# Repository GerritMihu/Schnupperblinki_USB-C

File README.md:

# Schnupperblinki_USB-C
 Schnupperübung für die Schupperschüler

 ## Bilder

## Exporte

- 3D-Ansichten:
  - [3D Top](./pic/3d_top.png)
  - [3D Bottom](./pic/3d_bottom.png)
  - [3D Isometrisch](./pic/3d_isometric.png)

- DXF (Layer-Exports): [dxf/](./dxf/)

### xTool Laser F2 Ultra — empfohlenes Vorgehensweise

- Empfohlen: zwei DXF-Dateien im dxf/-Ordner erzeugen:
  - Edge.Cuts → Schneidekante (äußerste Linie) — zum Schneiden
  - F.Cu     → Gravur (restliche Vektoren, kombiniert) 

Beispielbefehle:

# F.Cu (Gravur)
KICAD_CLI="kicad-cli" ./export_fcu_dxf.sh "Blinki mit USB-C.kicad_pcb" dxf

# Edge.Cuts (Schneiden)
flatpak run --command=kicad-cli org.kicad.KiCad pcb export dxf --layers Edge.Cuts --output-units mm --mode-single -o dxf "Blinki mit USB-C.kicad_pcb"

Hinweis: Die äußerste Linie (Edge.Cuts) ist die Schneidekante; der Rest wird als kombinierter Vektor für die Gravur genutzt. Falls Pfade gemerged oder Text in Konturen umgewandelt werden müssen, kann ein Zusatzskript oder Inkscape dafür genutzt; bei Bedarf hinzufügen.

## Bestückplan
[BOM (HTML-Preview)](https://htmlpreview.github.io/?https://github.com/GerritMihu/Schnupperblinki_USB-C/blob/main/bom/Blinki%20mit%20USB-C-ibom.html)

## Documentation exports

- PCB PDF: [Dok/Dok_PCB.pdf](./Dok/Dok_PCB.pdf)
- Schematic PDF: [Dok/Dok_SCH.pdf](./Dok/Dok_SCH.pdf)
- Schematic SVG: [Dok/Dok_SCH.svg](./Dok/Dok_SCH.svg)

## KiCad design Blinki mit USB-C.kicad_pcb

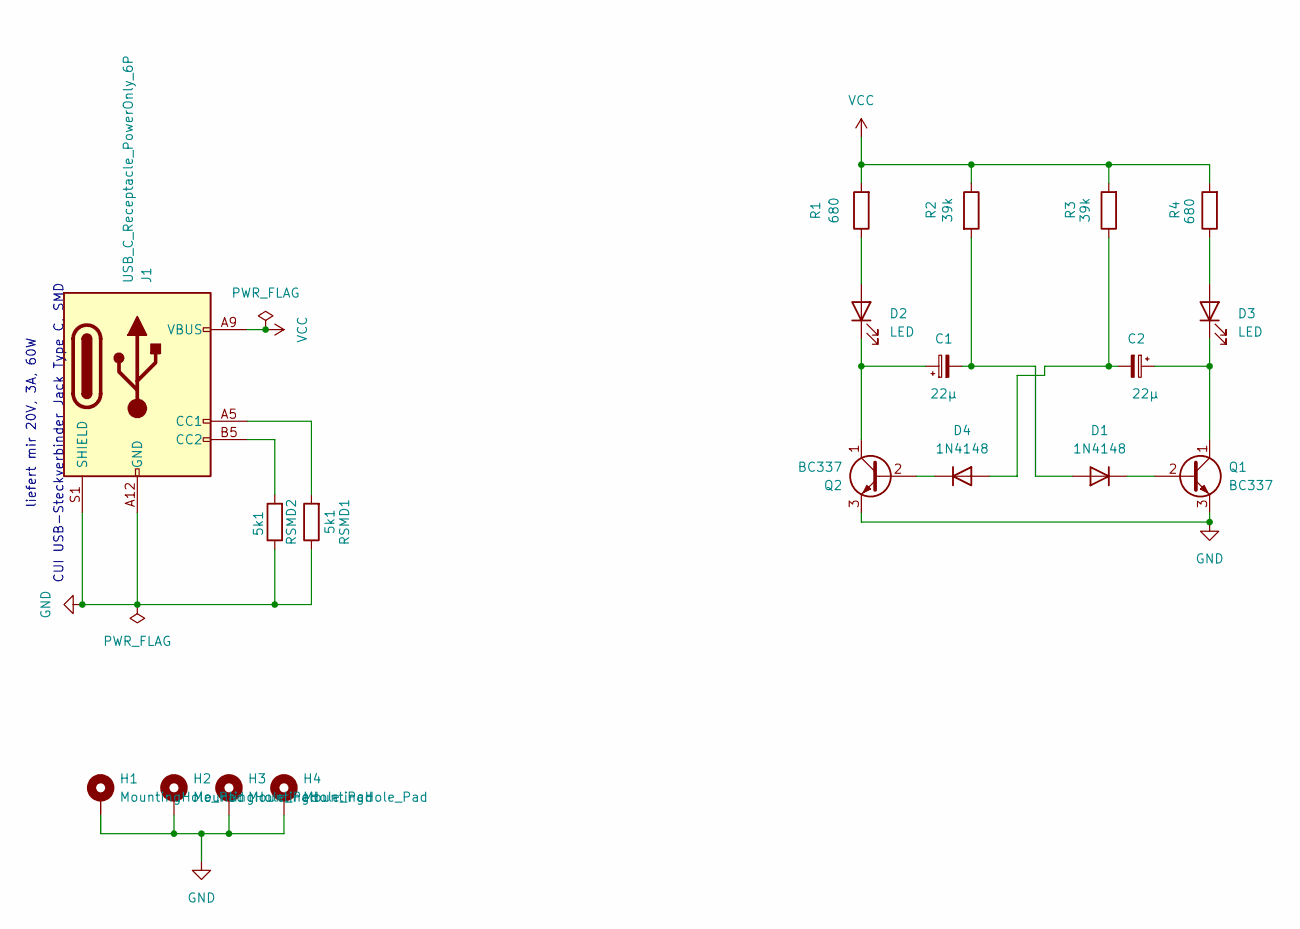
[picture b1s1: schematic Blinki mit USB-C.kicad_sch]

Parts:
C1, C2: 22µ; CP_Radial_D5.0mm_P2.50mm
D1, D4: 1N4148; D_DO-35_SOD27_P7.62mm_Horizontal
D2, D3: LED; LED_D3.0mm_FlatTop
H1, H2, H3, H4: MountingHole_Pad; MountingHole_3.2mm_M3
J1: USB_C_Receptacle_PowerOnly_6P
Q1, Q2: BC337; TO-92_Inline_Wide
R1, R4: 680; R_Axial_DIN0207_L6.3mm_D2.5mm_P10.16mm_Horizontal
R2, R3: 39k; R_Axial_DIN0207_L6.3mm_D2.5mm_P10.16mm_Horizontal
RSMD1, RSMD2: 5k1; R_0805_2012Metric_Pad1.20x1.40mm_HandSolder

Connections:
GND: H1.1, H2.1, H3.1, H4.1, J1.A12 (GND), J1.B12 (GND), J1.S1 (SHIELD), Q1.3 (E), Q2.3 (E), RSMD1.1, RSMD2.1
unnamed: C1.2, D1.2 (A), R2.2
unnamed: D1.1 (K), Q1.2 (B)
unnamed: D2.2 (A), R1.1
unnamed: C1.1, D2.1 (K), Q2.1 (C)
unnamed: D3.2 (A), R4.1
unnamed: C2.1, D3.1 (K), Q1.1 (C)
unnamed: C2.2, D4.2 (A), R3.1
unnamed: D4.1 (K), Q2.2 (B)
unnamed: J1.A5 (CC1), RSMD1.2
unnamed: J1.B5 (CC2), RSMD2.2
VCC: J1.A9 (VBUS), J1.B9 (VBUS), R1.2, R2.1, R3.2, R4.2

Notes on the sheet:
liefert mir 20V, 3A, 60W
CUI USB-Steckverbinder Jack Type C, SMD

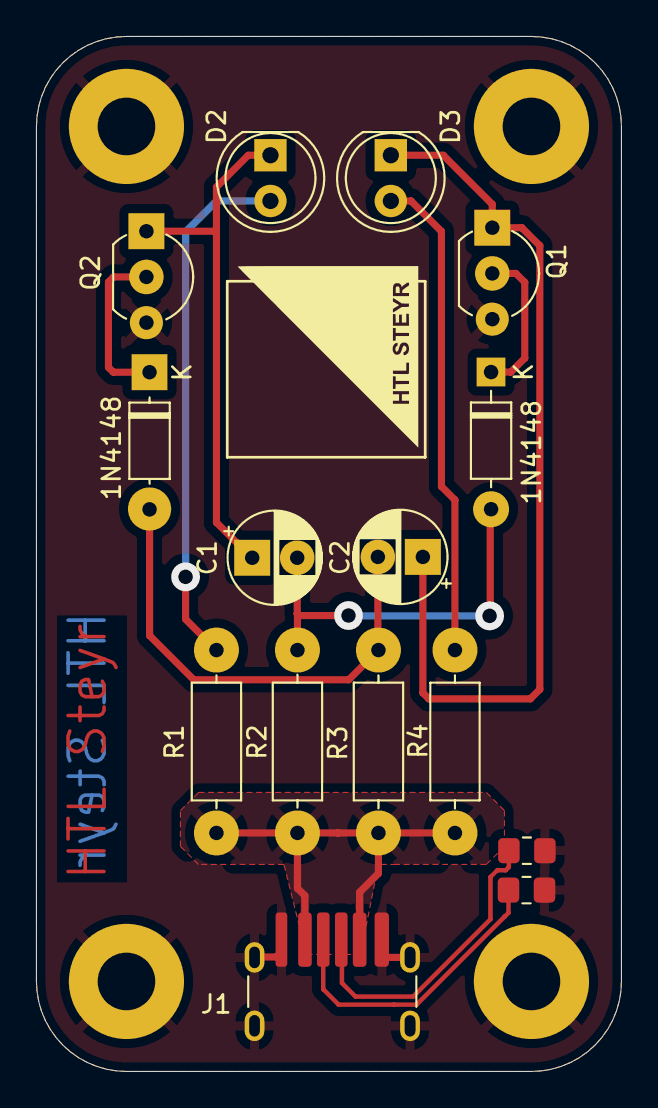
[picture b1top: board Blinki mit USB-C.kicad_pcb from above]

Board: 2 copper layers, 32.5 x 57.5 mm, 19 parts (0 on the bottom side), 12 nets.

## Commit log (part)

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2026-02-01 Updated Readme with pics and BOM
2026-02-01 dok created, title update
2026-05-23 feat: automate exports and update README preview links
    - Add update_readme.py to dynamically update the Interactive BOM preview link in README.md.
    - Integrate README update into export_all.py and export_all.sh.
    - Add GitHub Action workflow to automate KiCad exports and documentation updates on push.
    - Use KiCad nightly container in CI to support project file version.
    - Update .gitignore to exclude DXF export directory.
2026-05-23 ci: opt into Node.js 24 for GitHub Actions
